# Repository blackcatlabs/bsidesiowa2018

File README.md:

# B-Sides Iowa 2018 Badge

This is the repo serves as the project development page for the B-Sides Iowa badge

## Background 

* This badge serves as B-Sides Iowa's first electronic badge!
* Consequently primary design goals included low manufacturing costs and friendly user customization.  We wanted to create an electronic badge, but didn't want to risk blowing the bank for a small non-profit conference.
* Boards were manufactured with Seeed Fusion PCB
* Other cons are welcome to use this badge as a starting point for their own badges

## Badge Specs

* ATtiny85 Microcontroller, Internal Clock 
* 12x Charlieplexed LEDs
* 8K Flash
* Momentary Reset
* Programmable Header
* Powered via CR2032 coin cell

## Badge Functions:

* LED patterns
* Personalization
* GPIOs/SPI

## Third Party Tools

The following packages were used to create this badge
* Autodesk Eagle https://www.autodesk.com/products/eagle
* Arduino IDE https://www.arduino.cc/en/Main/Software
* Sparkfun AVR Programmer https://www.sparkfun.com/products/9825

You are certainly not limited to these packages.  Any AVR compiler/programmer will do, and KiCAD is also a top notch open source alternative to Eagle. 

### Prerequisites

Be sure to configure your compiler to use the ATtiny85.  Packages are available at
https://raw.githubusercontent.com/damellis/attiny/ide-1.6.x-boards-manager/package_damellis_attiny_index.json

### Uploading firmware to badge

1. Either use an AVR programmer with POGO pins or solder a 2x3 header to the board
2. Connect the AVR programmer to the header, ensuring to match the orientation for pin 1.  (If you are using a POGO adapter at the conference, just flip the board upside down such that the microcontroller is showing.  Orient the adapter such that the ribbon cable is directly above the microcontroller.
3. Upload the code!

## Authors / Contributors

* **G Rice**

## Acknowledgments

* Tip of of the hat to D. Darko for the Tri-State Pulse Width Modulator
* Thanks to the Seeed team for the great CAM service and inspection
* Special thanks to the B-Sides sponsors for making this badge a reality

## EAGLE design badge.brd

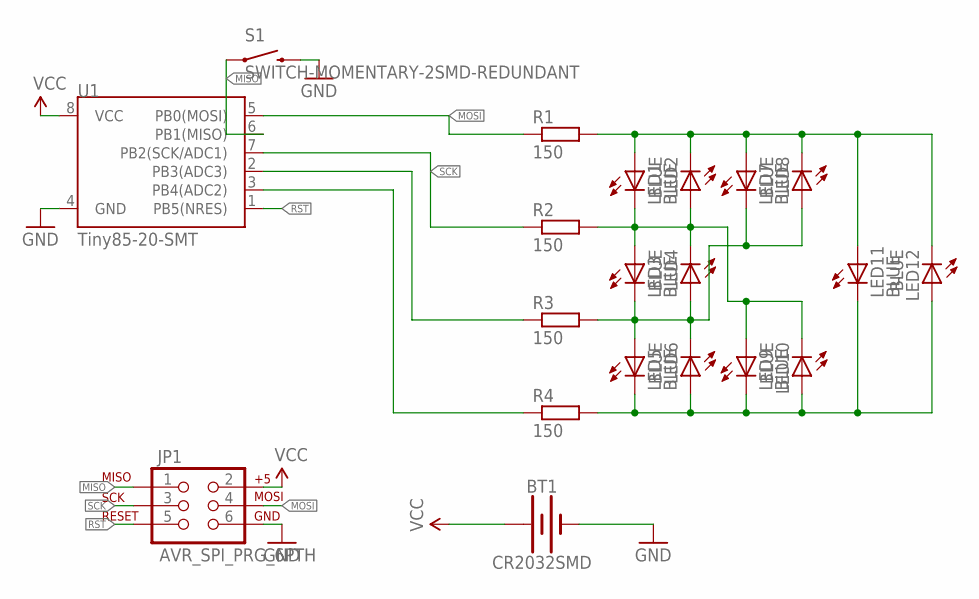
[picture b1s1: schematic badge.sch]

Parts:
BT1: CR2032SMD; BATTCON_20MM_4LEGS
JP1: AVR_SPI_PRG_6PTH; 2X3
LED1, LED2, LED3, LED4, LED5, LED6, LED7, LED8, LED9, LED10, LED11, LED12: BLUE; CHIP-LED0805
R1, R2, R3, R4: 150; R0805
S1: SWITCH-MOMENTARY-2SMD-REDUNDANT; TACTILE-SWITCH-SMD
U1: Tiny85-20-SMT; SO08-EIAJ

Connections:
GND: BT1.NEGATIVE (GND), JP1.6, S1.3 (2), S1.4 (2), U1.4 (GND)
MISO: JP1.1, S1.1, S1.2 (1), U1.6 (PB1(MISO))
MOSI: JP1.4, R1.1, U1.5 (PB0(MOSI))
unnamed: R4.1, U1.3 (PB4(ADC2))
unnamed: LED5.C, LED6.A, LED9.C, LED10.A, LED11.C, LED12.A, R4.2
unnamed: LED1.A, LED2.C, LED7.A, LED8.C, LED11.A, LED12.C, R1.2
unnamed: LED1.C, LED2.A, LED3.A, LED4.C, LED9.A, LED10.C, R2.2
unnamed: LED3.C, LED4.A, LED5.A, LED6.C, LED7.C, LED8.A, R3.2
PB3: R3.1, U1.2 (PB3(ADC3))
RST: JP1.5, U1.1 (PB5(NRES))
SCK: JP1.3, R2.1, U1.7 (PB2(SCK/ADC1))
VCC: BT1.POSITIVE@1 (VCC), BT1.POSITIVE@2 (VCC), BT1.POSITIVE@3 (VCC), BT1.POSITIVE@4 (VCC), JP1.2, U1.8 (VCC)

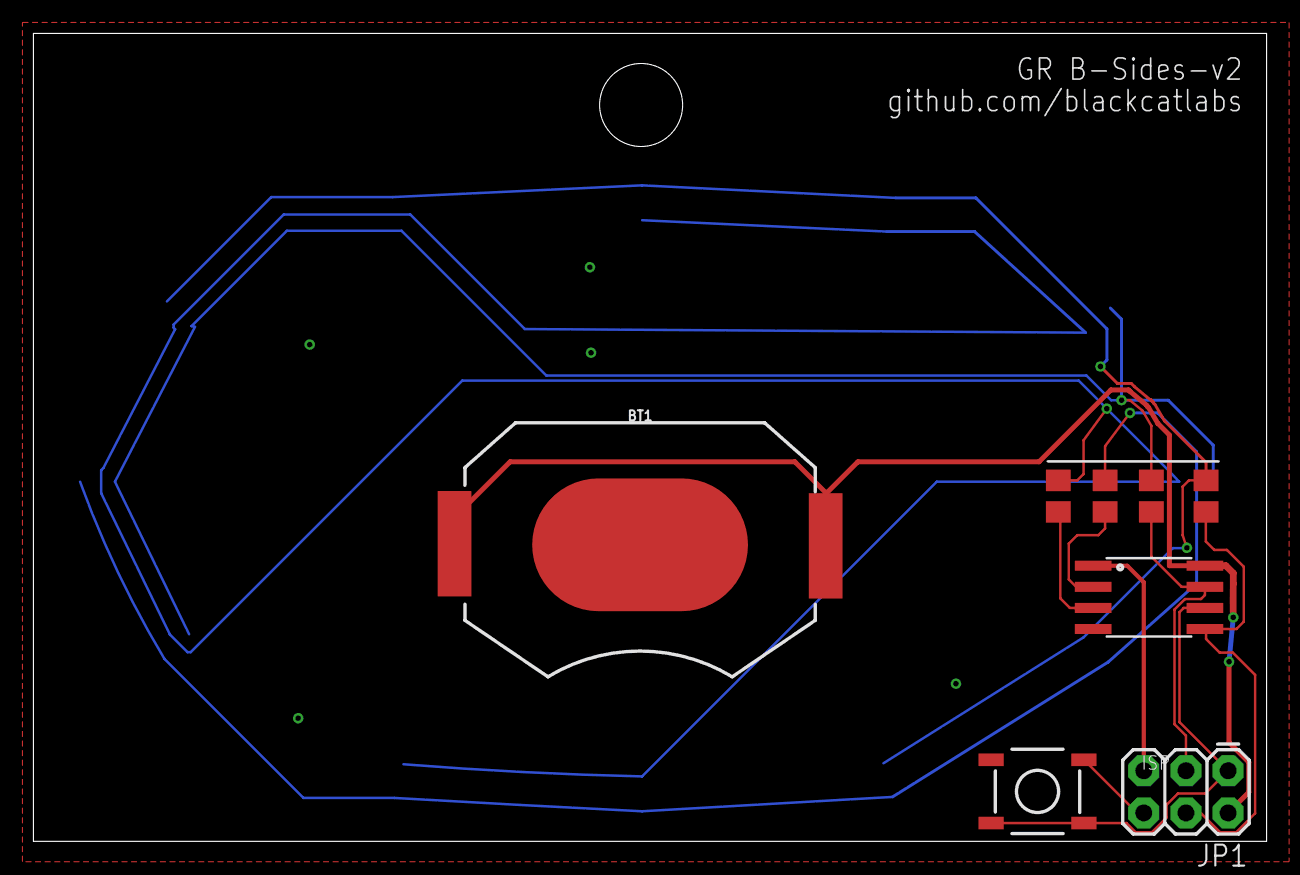
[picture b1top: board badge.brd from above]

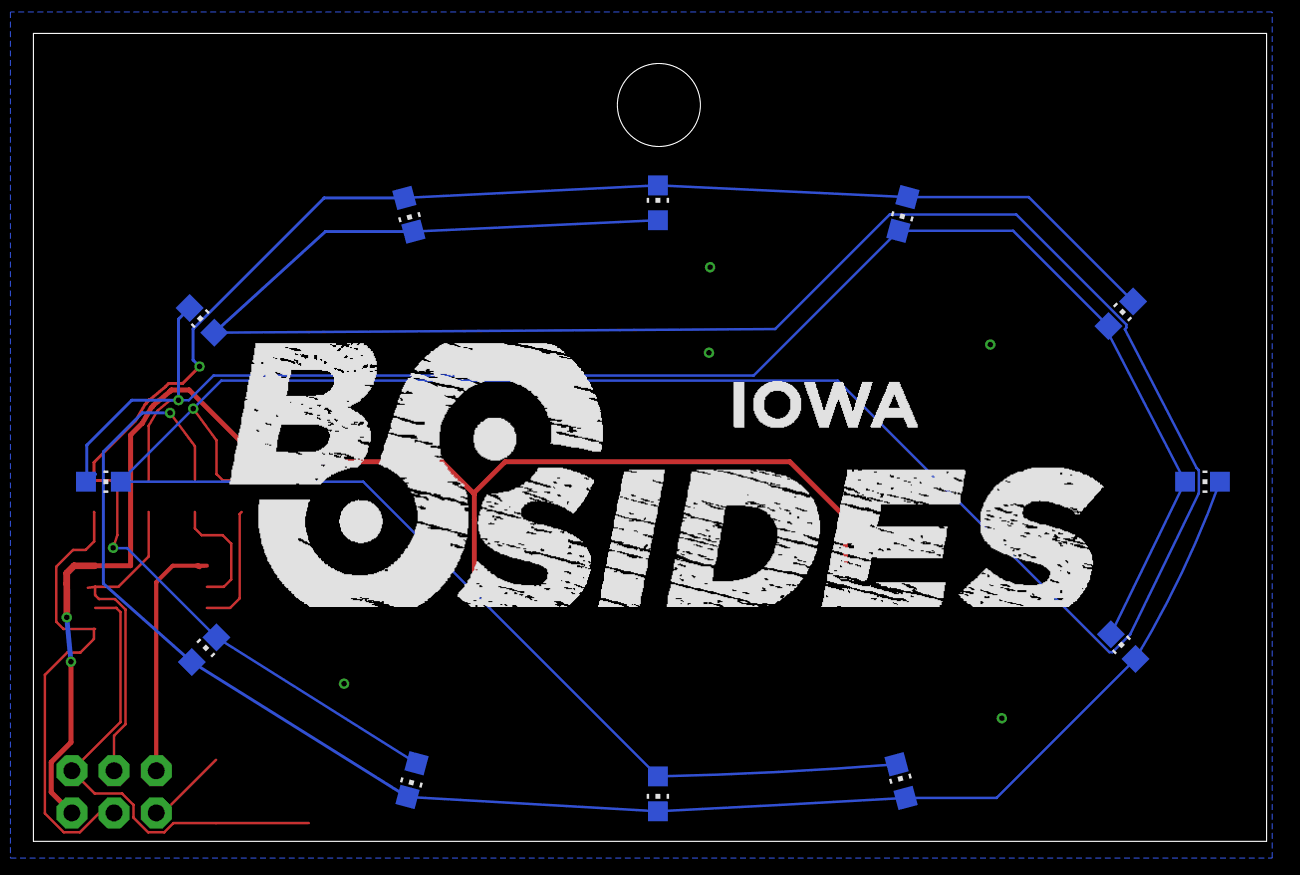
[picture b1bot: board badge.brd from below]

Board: 2 copper layers, 74.3 x 48.7 mm, 20 parts (12 on the bottom side), 12 nets.

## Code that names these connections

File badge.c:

/* 
 * This file is part of the B-Sides Iowa 2018 badge 
 * <https://github.com/blackcatlabs/bsidesiowa2018>
 * Copyright (c) 2018 B-Sides Iowa.
 * 
 * This program is free software: you can redistribute it and/or modify  
 * it under the terms of the GNU General Public License as published by  
 * the Free Software Foundation, version 3.
 *
 * This program is distributed in the hope that it will be useful, but 
 * WITHOUT ANY WARRANTY; without even the implied warranty of 
 * MERCHANTABILITY or FITNESS FOR A PARTICULAR PURPOSE. See the GNU 
 * General Public License for more details.
 *
 * You should have received a copy of the GNU General Public License 
 * along with this program. If not, see <http://www.gnu.org/licenses/>.
 */


#include <avr/sleep.h>
#include <avr/io.h>
#define nop() asm volatile("nop")

// ==================================================================================
//                ATtiny85
//              +--------+
//            --+ o  Vcc +------------
//  LED - PB3 --+        +-- PB2 - LED
//  LED - PB4 --+        +-- PB1 - RST
//  ------------+ GND    +-- PB0 - LED
//              +--------+
//
// If you are new to AVR microcontrollers, the following cheat sheet may be helpful:
//  PORTB :  Port B Data Register
//  PBn   :  Port B, Pin N
//  DDRB  :  Data direction register 
//
// For additional information, please refer to the ATtiny85 datasheet: 
// <https://www.mouser.com/ds/2/268/Atmel-2586-AVR-8-bit-Microcontroller-ATtiny25-ATti-1066528.pdf>
//
// Note: This software has been developed with novice readability in mind. Experts are 
//       encouraged to make modifications to preserve code space.  Familiarizing yourself  
//       with the PortB registers and their corresponding register bit effects can serve  
//       to conserve overall code space.    
// ==================================================================================

// Define the I/O ports to be used for the LEDs
#define LED_PIN0 PB0
#define LED_PIN1 PB2
#define LED_PIN2 PB3
#define LED_PIN3 PB4
#define RESET    PB1

boolean leds_on = true;

// Interrupt service routine
ISR(INT0_vect) {
   sleep_disable();
   leds_on = true;
}

// Setup runs once; this initializes the badge
void setup() {
   // Set the reset port pin as an input
   // All other pins will act as LED output
   digitalWrite(RESET, HIGH);
   pinMode(PB1, INPUT_PULLUP);
   
   pinMode(LED_PIN0, OUTPUT);
   pinMode(LED_PIN1, OUTPUT);
   pinMode(LED_PIN2, OUTPUT);
   pinMode(LED_PIN3, OUTPUT);

   // To conserve battery power, set to sleep mode
   sleep();
}

// This is the main routine of the program
void loop() {

   if (leds_on)
   {
      // Disable global interrupts
      cli();
      leds_on = false;
   }

   // Check for reset
   // If reset is active, do something special to sanity check
   if (!(digitalRead(RESET)))
   {
      charlieplexpin(5);
      delay(10);
      leds_off();
      delay(10);
      charlieplexpin(11);
      delay(200);
      sleep();
   }
   else
   {
      animate_leds();
   }
}

// Set the microcontroller into the sleep state 
// System wakes up when watchdog times out
void sleep()
{
   leds_off();

   // Disable the watchdog by performing the following steps:
   // Clear watchdog reset flag in the MCU status register 
   MCUSR &= ~(1 << WDRF);
   // Enable the watchdog timer
   WDTCR |= (1 << WDCE) | (1 << WDE);
   // Turn off the watchdog timer
   WDTCR = 0x00;

   // Turn off the ADC to save further power
   ADCSRA &= ~(1 << ADEN); 

   // Enable external interrupts on pin change
   GIMSK |= (1 << INT0);
   GIMSK |= (1 << PCIE);

   // Set sleep mode to conserve power
   set_sleep_mode(SLEEP_MODE_PWR_DOWN);
   sleep_enable();
   // Enable system interrupts
   sei(); 
   // System actually sleeps here
   sleep_cpu();
   
   // System continues here on interrupt
   sleep_disable();
}

void animate_leds()
{
   // Light clockwise
   for (int i = 0; i < 12; i++) {
      charlieloop(i);
   }

   // Light counterclockwise
   for (int i = 11; i >= 0; i--) {
      charlieloop(i);
   }

   // Blink top last time
   charlieloop(11);
}

// The ATtiny has relatively few I/O pins, so we drive the LEDs using a
// technique knoqn as charlieplexing.  The method uses tri-state logic
// For more info: <https://en.wikipedia.org/wiki/Charlieplexing>
void charlieloop(int pin)
{
   for (int j=0; j<4096; j++)
   {
      // This should ideally be cleaned up with better timing, but
      // it works for the moment...  Credits to darko for the PWM 
      charlieplexpin(pin);
      nop();
      nop();
      nop();
      nop();
      leds_off();
      nop();
      nop();
      nop();
      nop();
      nop();
      nop();
      nop();
      nop();
      nop();
      nop();
   }
}

void leds_off()
{
   DDRB &= ~((1 << LED_PIN0) | (1 << LED_PIN1) | (1 << LED_PIN2) | (1 << LED_PIN3));
   PORTB &= ~((1 << LED_PIN0) | (1 << LED_PIN1) | (1 << LED_PIN2) | (1 << LED_PIN3));
}

void  charlieplexpin(int id) 
{
   leds_off();

   switch (id) {
     case 0: 
      DDRB |= (1 << LED_PIN0) | (1 << LED_PIN1); 
      PORTB |= (1 << LED_PIN0);  // HIGH
      // Equivalent to digitalWrite(LED_PIN0, HIGH) 
      // We alter the registers directly for the sake of speed 
      // and a smoother animation
      PORTB &= ~(1 << LED_PIN1); // LOW
      break;
    case 1: 
      DDRB |= (1 << LED_PIN0) | (1 << LED_PIN1); 
      PORTB |= (1 << LED_PIN1);  // HIGH
      PORTB &= ~(1 << LED_PIN0); // LOW
      break;
    case 2: 
      DDRB |= (1 << LED_PIN1) | (1 << LED_PIN2); 
      PORTB |= (1 << LED_PIN1);  // HIGH
      PORTB &= ~(1 << LED_PIN2); // LOW
      break;
    case 3: 
      DDRB |= (1 << LED_PIN1) | (1 << LED_PIN2); 
      PORTB |= (1 << LED_PIN2);  // HIGH
      PORTB &= ~(1 << LED_PIN1); // LOW
      break;
    case 4: 
      DDRB |= (1 << LED_PIN2) | (1 << PB4); 
      PORTB |= (1 << LED_PIN2);  // HIGH
      PORTB &= ~(1 << PB4);      // LOW
      break;
    case 5: 
      DDRB |= (1 << LED_PIN2) | (1 << PB4); 
      PORTB |= (1 << PB4);       // HIGH
      PORTB &= ~(1 << LED_PIN2); // LOW
      break;
    case 6: 
      DDRB |= (1 << LED_PIN0) | (1 << LED_PIN2); 
      PORTB |= (1 << LED_PIN0);  // HIGH
      PORTB &= ~(1 << LED_PIN2); // LOW
      break;
    case 7: 
      DDRB |= (1 << LED_PIN0) | (1 << LED_PIN2); 
      PORTB |= (1 << LED_PIN2);  // HIGH
      PORTB &= ~(1 << LED_PIN0); // LOW
      break;
    case 8: 
      DDRB |= (1 << LED_PIN1) | (1 << LED_PIN3); 
      PORTB |= (1 << LED_PIN1);  // HIGH
      PORTB &= ~(1 << LED_PIN3); // LOW
      break;
    case 9: 
      DDRB |= (1 << LED_PIN1) | (1 << LED_PIN3); 
      PORTB |= (1 << LED_PIN3);  // HIGH
      PORTB &= ~(1 << LED_PIN1); // LOW
      break;
    case 10: 
      DDRB |= (1 << LED_PIN0) | (1 << LED_PIN3); 
      PORTB |= (1 << LED_PIN0);  // HIGH
      PORTB &= ~(1 << LED_PIN3); // LOW
      break;
    case 11: 
      DDRB |= (1 << LED_PIN0) | (1 << LED_PIN3); 
      PORTB |= (1 << LED_PIN3);  // HIGH
      PORTB &= ~(1 << LED_PIN0); // LOW
      break;
   }
}

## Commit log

2018-04-14 Easy circuit view

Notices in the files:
parts and their libraries:
SparkFun-DigitalIC: Licensing: Creative Commons ShareAlike 4.0 International - https://creativecommons.org/licenses/by-sa/4.0
